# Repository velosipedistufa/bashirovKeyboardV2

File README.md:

to install ergogen
npm i -g ergogen

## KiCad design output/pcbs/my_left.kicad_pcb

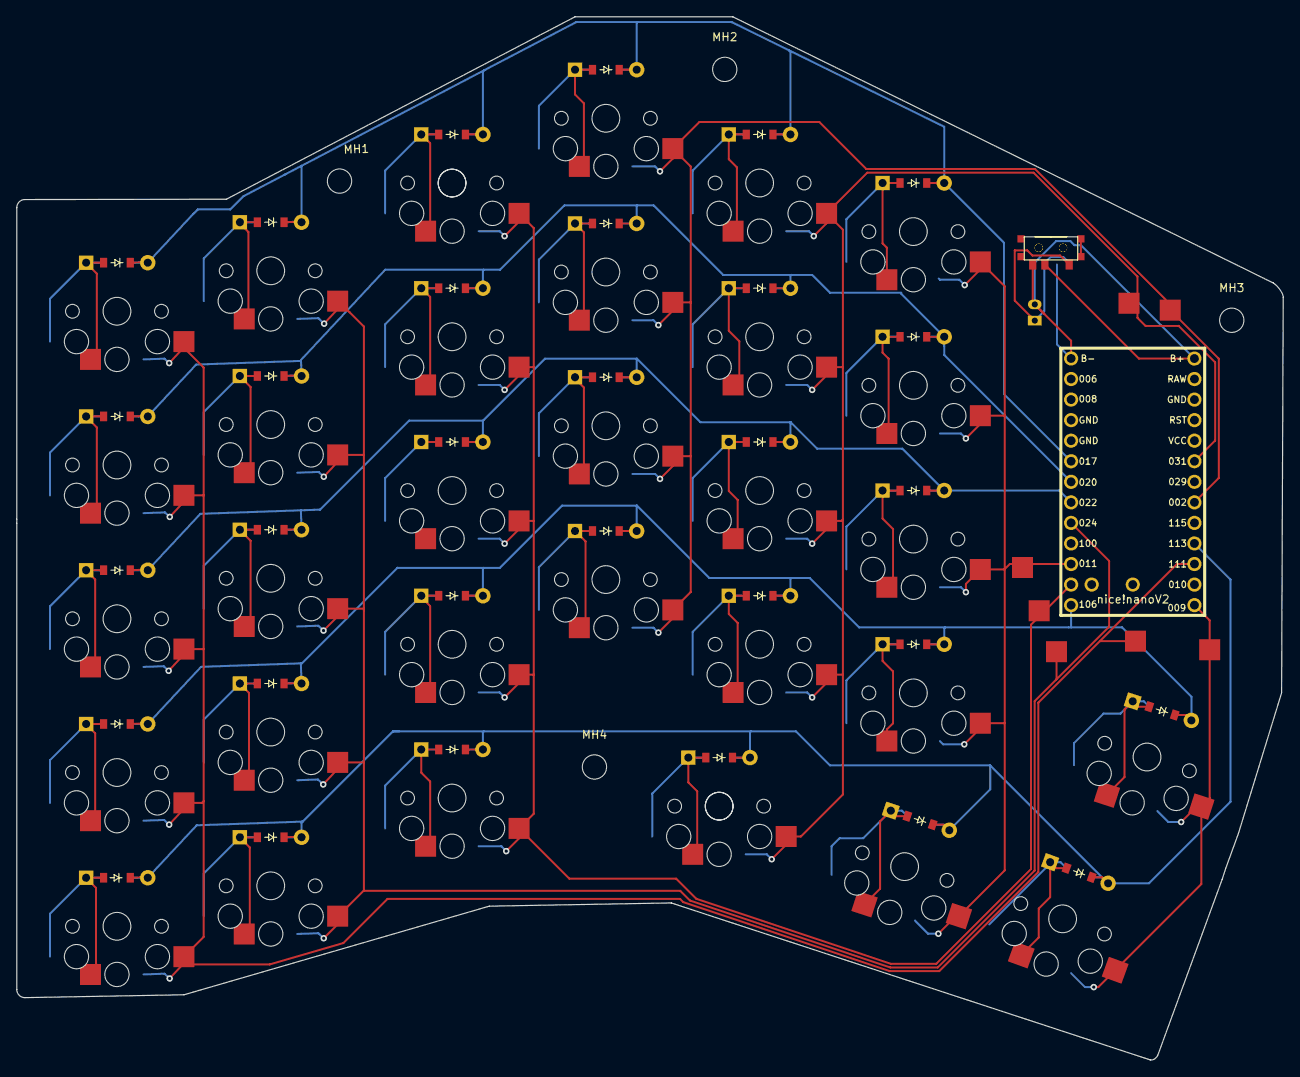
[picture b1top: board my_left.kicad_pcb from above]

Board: 2 copper layers, 156.5 x 128.9 mm, 70 parts (1 on the bottom side), 15 nets.

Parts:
D1, D1#2, D3, D4, D5, D6, D7, D8, D9, D10, D11, D12, D13, D14, D15, D16, D17, D18, D19, D20, D21, D22, D23, D24, D24#2, D25, D26, D27, D28, D28#2, D28#3: ComboDiode
JST1: JST_PH_S2B-PH-K_02x2.00mm_Angled
MCU1: nice_nano
MH1, MH2, MH3, MH4: MountingHole_3mm
S1, S2, S3, S4, S5, S6, S7, S8, S9, S10, S11, S12, S13, S14, S15, S16, S17, S18, S19, S20, S21, S22, S23, S24, S25, S26, S27, S28, S29, S30, S31: PG1350
T1, T1#2: SPDT_C128955

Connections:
GND: JST1.2, MCU1.0, T1.2, T1#2.3
RAW: JST1.1, T1.3, T1#2.1
VCC: MCU1.25, T1.1, T1#2.2
home_default: MCU1.10, S24.1, S24.2, S25.1, S25.2, S26.1, S26.2, S27.2, S30.1, S30.2
inner_bottom: D1#2.2, D7.2, D12.2, D16.2, D20.2, D24#2.2, D28#3.2, MCU1.12
inner_home: D3.2, D8.2, D13.2, D17.2, D21.2, D25.2, MCU1.7
inner_num: D5.2, D10.2, D15.2, D19.2, D23.2, D27.2, MCU1.5
inner_top: D4.2, D9.2, D14.2, D18.2, D22.2, D26.2, MCU1.6
outer_default: MCU1.15, S1.1, S1.2, S2.1, S2.2, S3.1, S3.2, S4.1, S4.2, S5.1, S5.2
outer_frow: D1.2, D6.2, D11.2, D24.2, D28.2, D28#2.2, MCU1.16
pinky_frow: MCU1.18, S16.1, S16.2, S17.1, S17.2, S18.1, S18.2, S19.1, S19.2
pinky_home: MCU1.11, S11.1, S11.2, S12.1, S12.2, S13.1, S13.2, S14.1, S14.2, S15.1, S15.2
pinky_num: MCU1.8, S6.1, S6.2, S7.1, S7.2, S8.1, S8.2, S9.1, S9.2, S10.1, S10.2
pinky_top: MCU1.20, S20.1, S20.2, S21.1, S21.2, S22.1, S22.2, S23.1, S23.2, S29.1, S29.2
thumb_bottom: MCU1.13, S28.1, S28.2, S31.1, S31.2

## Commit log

2026-03-28 started tracing
2026-03-28 replaced nice nano pcb footprint
2026-04-11 order next week
2026-04-15 polished pcb, generated gerber files
